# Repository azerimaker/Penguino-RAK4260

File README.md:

# Penguino-RAK4260
This repo contains all the necessary design and fabrication files for the Penguino 4260 SAMR34 Feather breakout board. 

First prototypes are being sold on [Tindie](https://www.tindie.com/products/21143/) and some more info can also be found on the corresponding [hackaday.io](https://hackaday.io/project/168876-penguino-feather-samr34-lora-dev-board) project page. This Penguino version uses [RAK4260](https://rakwireless.kckb.st/9e150da0) module. 

________________________________

### Current HW version is:
Penguino Feather v1.2. 
- Comes with green soldermask
- Adds CH340E USB-UART Converter IC

________________________________

### Example Firmware

Povided example in the *Firmware* directory contains ready to use example projetcs for Atmel Studio v7.
- RGB LED Toggle 
- LoRaWAN UART Demo

## License:
- Hardware license: CERN-OHL-S v2
- Software license: under MIT unless otherise indicated 
- Documentation license:  CC BY-SA 4.0 International.
________________________________
## Open Source Hardware
This board is an OSHWA approved design: [AZ000001](https://certification.oshwa.org/az000001.html)

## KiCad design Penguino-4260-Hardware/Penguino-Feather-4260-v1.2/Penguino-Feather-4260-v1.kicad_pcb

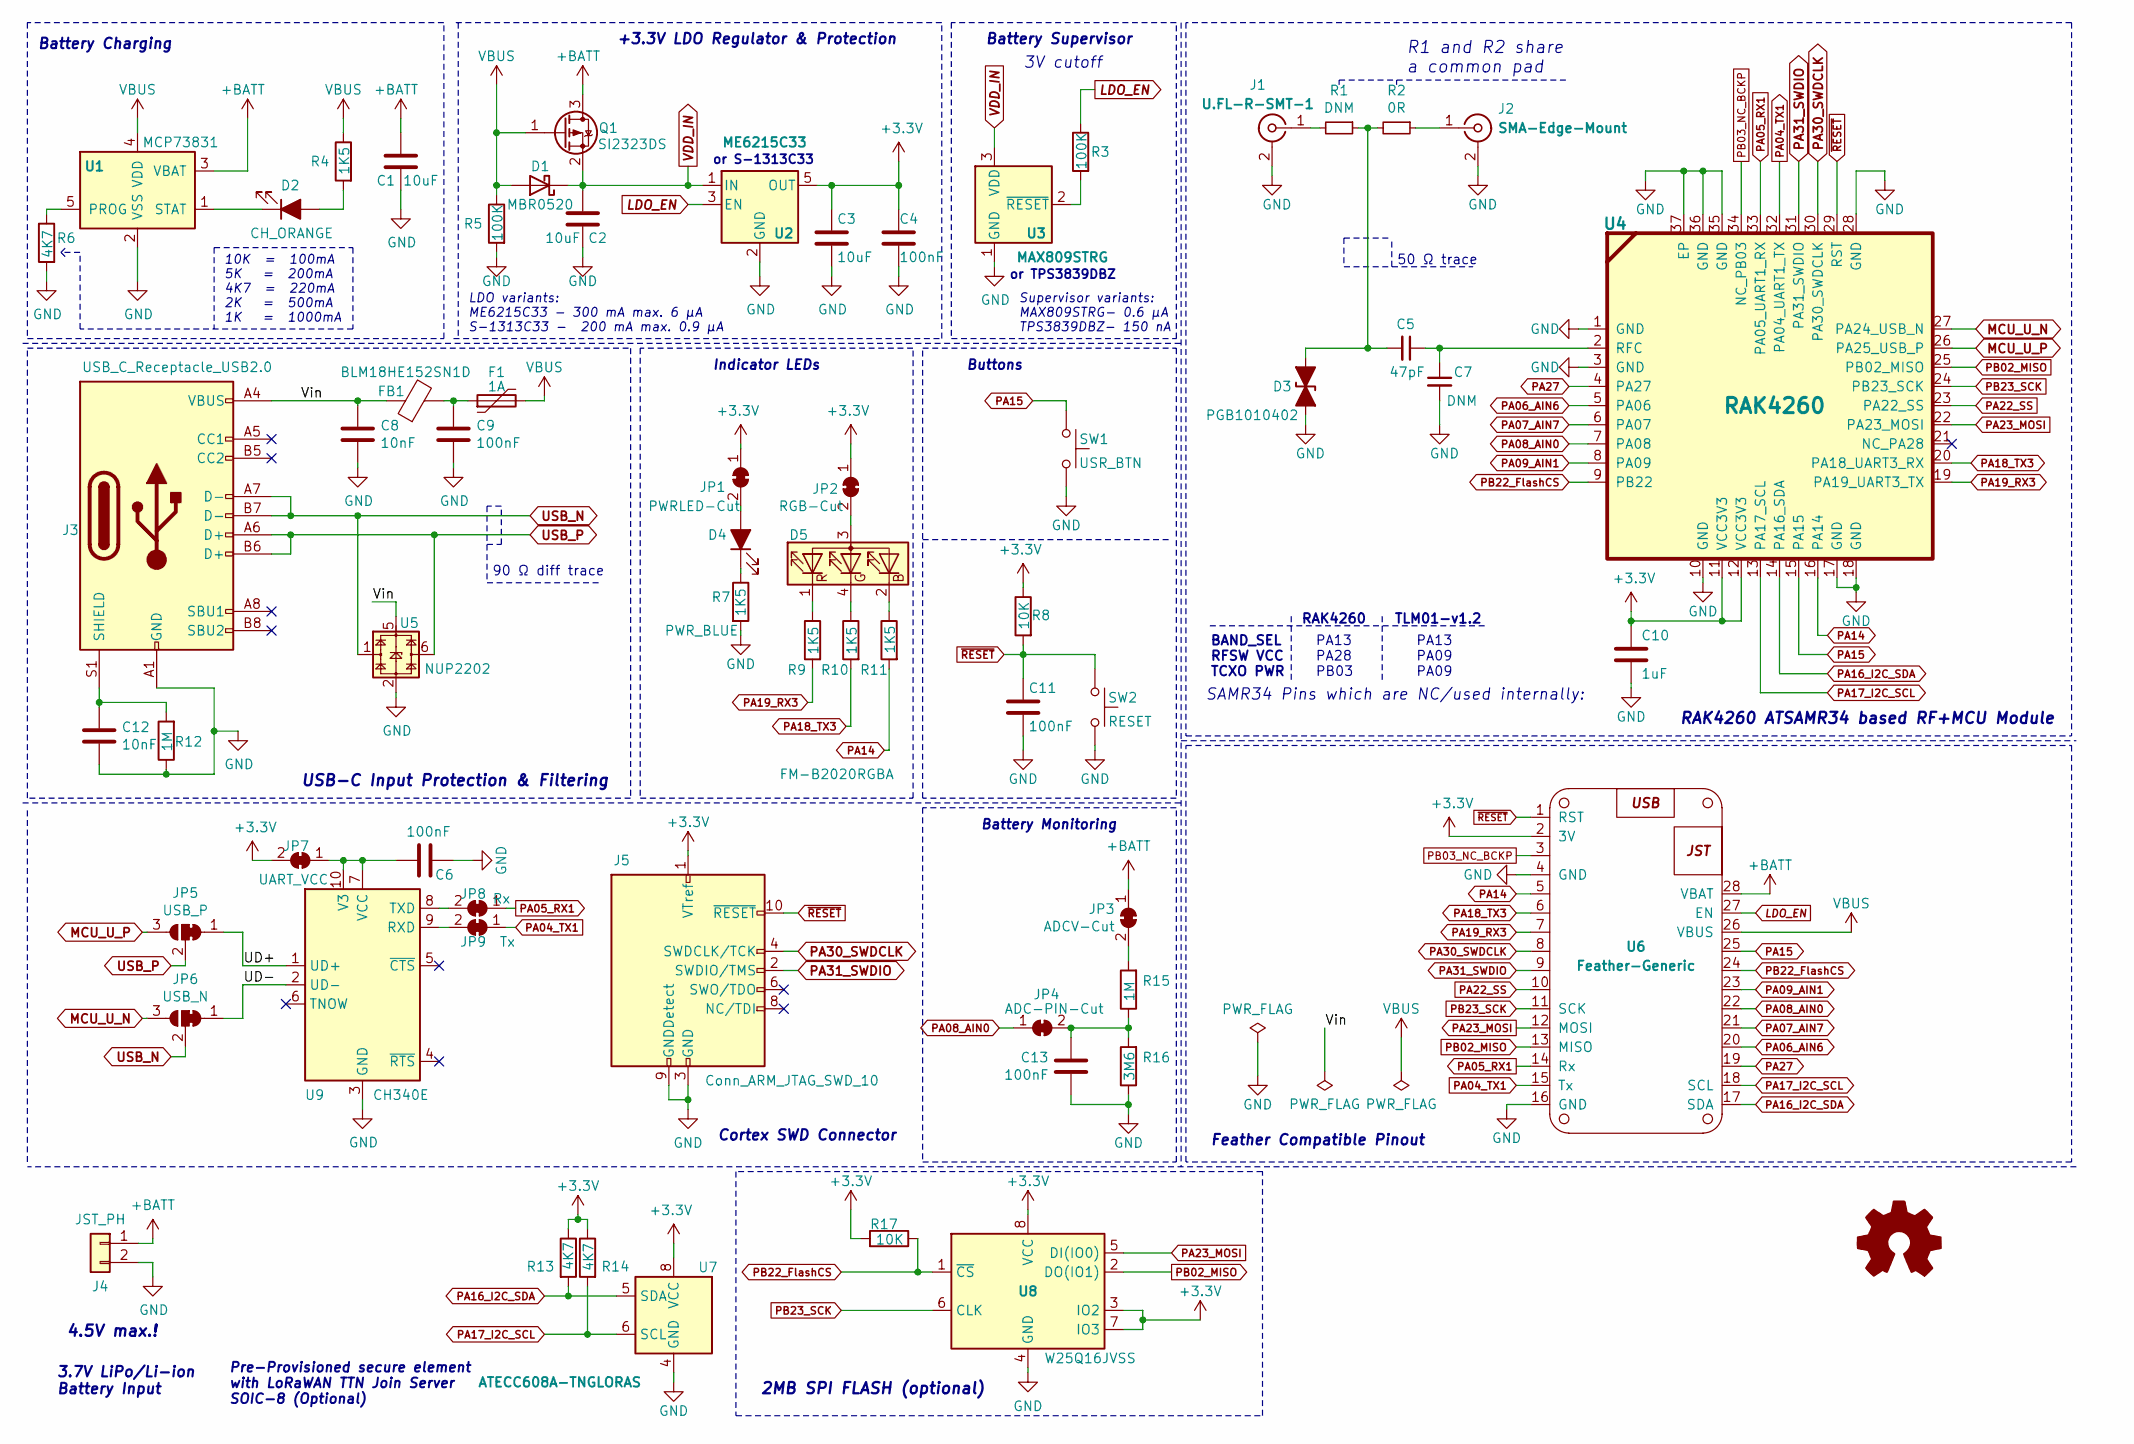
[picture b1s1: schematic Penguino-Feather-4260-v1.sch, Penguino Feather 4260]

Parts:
C1, C2, C3: 10uF; C_0603_1608Metric
C4, C6, C9: 100nF; C_0603_1608Metric; MPN CC0603KRX7R9BB104
C5: 47pF; C_0402_1005Metric
C7: DNM; C_0402_1005Metric
C8, C12: 10nF; C_0603_1608Metric; MPN CC0603KRX7R9BB103
C10: 1uF; C_0603_1608Metric; MPN CC0603KRX7R8BB105
C11, C13: 100nF; C_0402_1005Metric; MPN CC0603KRX7R9BB104
D1: MBR0520; D_SOD-123; MPN MBR0520
D2: CH_ORANGE; LED_0603_1608Metric
D3: PGB1010402; L_0402_1005Metric; MPN PGB1010402KR
D4: PWR_BLUE; LED_0603_1608Metric
D5: FM-B2020RGBA; LED_Cree-PLCC4_2x2mm_CW; MPN FM-B2020RGBA-HG
F1: 1A; Fuse_0805_2012Metric; MPN 0805L110SLYR
FB1: BLM18HE152SN1D; L_0603_1608Metric; MPN BLM18HE152SN1D
J1: U.FL-R-SMT-1; U.FL_Hirose_U.FL-R-SMT-1_Vertical; MPN U.FL-R-SMT-1(80)
J2: SMA-Edge-Mount; SMA_J_P_X_ST_EM1_EdgeMount; MPN SMA-J-P-H-ST-EM1
J3: USB_C_Receptacle_USB2.0; USB_C_Receptacle_Palconn_UTC16-G; MPN TYPE-C-31-M-12
J4: JST_PH; JST_PH_S2B-PH-SM4-TB_1x02-1MP_P2.00mm_Horizontal; MPN S2B-PH-SM4-TB(LF)(SN)
J5: Conn_ARM_JTAG_SWD_10; PinHeader_2x05_P1.27mm_Vertical_SMD
JP1: PWRLED-Cut; SolderJumper-2_P1.3mm_Bridged_RoundedPad1.0x1.5mm
JP2: RGB-Cut; SolderJumper-2_P1.3mm_Bridged_RoundedPad1.0x1.5mm
JP3: ADCV-Cut; SolderJumper-2_P1.3mm_Bridged_RoundedPad1.0x1.5mm
JP4: ADC-PIN-Cut; SolderJumper-2_P1.3mm_Bridged_RoundedPad1.0x1.5mm
JP5: USB_P; SolderJumper-3_P1.3mm_Bridged12_Pad1.0x1.5mm
JP6: USB_N; SolderJumper-3_P1.3mm_Bridged12_Pad1.0x1.5mm
JP7: UART_VCC; SolderJumper-2_P1.3mm_Bridged_RoundedPad1.0x1.5mm
JP8: Rx; SolderJumper-2_P1.3mm_Bridged_RoundedPad1.0x1.5mm
JP9: Tx; SolderJumper-2_P1.3mm_Bridged_RoundedPad1.0x1.5mm
Q1: SI2323DS; SOT-23; MPN SI2323DS-T1-E3
R1: DNM; R_0402_1005Metric
R2: 0R; R_0402_1005Metric
R3, R5: 100K; R_0402_1005Metric
R4, R7, R9, R10, R11: 1K5; R_0402_1005Metric
R6, R13, R14: 4K7; R_0402_1005Metric
R8, R17: 10K; R_0402_1005Metric
R12, R15: 1M; R_0402_1005Metric
R16: 3M6; R_0402_1005Metric; MPN RC0402JR-073M6L
SW1: USR_BTN; SW_Push_SKRPACE010; MPN SKRPACE010
SW2: RESET; SW_Push_SKRPACE010; MPN SKRPACE010
U1: MCP73831; SOT-23-5; MPN MCP73831-2-OT
U2: ME6215C33; SOT-23-5; MPN ME6215C33
U3: MAX809STRG; SOT-23; MPN MAX809STRG
U4: RAK4260; RAK4260-footprint_w_solder_paste
U5: NUP2202; SOT-363_SC-70-6; MPN NUP2202W1T2G
U6: Feather-Generic
U7: ATECC608A-TNGLORAS; SOIC-8_3.9x4.9mm_P1.27mm; MPN ATECC608A-TNGLORAS-B
U8: W25Q16JVSS; SOIC-8_5.23x5.23mm_P1.27mm
U9: CH340E; MSOP-10_3x3mm_P0.5mm

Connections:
+3V3: C3.1, C4.1, C10.1, J5.1 (VTref), JP1.1 (A), JP2.1 (A), JP7.2 (B), R8.1, R13.1, R14.1, R17.2, U2.5 (OUT), U4.11 (VCC3V3), U4.12 (VCC3V3), U6.2 (3V), U7.8 (VCC), U8.3 (IO2), U8.7 (IO3), U8.8 (VCC)
+BATT: C1.1, J4.1, JP3.1 (A), Q1.3 (D), U1.3 (VBAT), U6.28 (VBAT)
/UD+: JP5.1 (A), U9.1 (UD+)
/UD-: JP6.1 (A), U9.2 (UD-)
/Vin: C8.1, FB1.1, J3.A4 (VBUS), J3.A9 (VBUS), J3.B4 (VBUS), J3.B9 (VBUS), U5.5
GND: C1.2, C2.2, C3.2, C4.2, C6.1, C7.2, C8.2, C9.2, C10.2, C11.2, C12.1, C13.1, D3.2 (A2), J1.2 (Ext), J2.2 (Ext), J3.A1 (GND), J3.A12 (GND), J3.B1 (GND), J3.B12 (GND), J4.2, J5.3 (GND), J5.5 (GND), J5.9 (GNDDetect), R5.2, R6.2, R7.2, R12.1, R16.1, SW1.1, SW2.1, U1.2 (VSS), U2.2 (GND), U3.1 (GND), U4.1 (GND), U4.3 (GND), U4.10 (GND), U4.17 (GND), U4.18 (GND), U4.28 (GND), U4.35 (GND), U4.36 (GND), U4.37 (EP), U5.2, U6.4 (GND), U6.16 (GND), U7.4 (GND), U8.4 (GND), U9.3 (GND)
LDO_EN: R3.1, U2.3 (EN), U6.27 (EN)
MCU_U_N: JP6.3 (B), U4.27 (PA24_USB_N)
MCU_U_P: JP5.3 (B), U4.26 (PA25_USB_P)
unnamed: C5.1, C7.1, U4.2 (RFC)
unnamed: C5.2, D3.1 (A1), R1.1, R2.2
unnamed: C6.2, JP7.1 (A), U9.7 (VCC), U9.10 (V3)
unnamed: C9.1, F1.1, FB1.2
unnamed: C12.2, J3.S1 (SHIELD), R12.2
unnamed: C13.2, JP4.2 (B), R15.1, R16.2
unnamed: D2.1 (K), U1.1 (STAT)
unnamed: D2.2 (A), R4.2
unnamed: D4.1 (K), R7.1
unnamed: D4.2 (A), JP1.2 (B)
unnamed: D5.1 (RK), R9.1
unnamed: D5.2 (BK), R11.1
unnamed: D5.3 (A), JP2.2 (B)
unnamed: D5.4 (GK), R10.1
unnamed: J1.1 (In), R1.2
unnamed: J2.1 (In), R2.1
unnamed: JP3.2 (B), R15.2
unnamed: JP8.2 (B), U9.8 (TXD)
unnamed: JP9.2 (B), U9.9 (RXD)
unnamed: R3.2, U3.2 (~RESET)
unnamed: R6.1, U1.5 (PROG)
PA04_TX1: JP9.1 (A), U4.32 (PA04_UART1_TX), U6.15 (Tx)
PA05_RX1: JP8.1 (A), U4.33 (PA05_UART1_RX), U6.14 (Rx)
PA06_AIN6: U4.5 (PA06), U6.20
PA07_AIN7: U4.6 (PA07), U6.21
PA08_AIN0: JP4.1 (A), U4.7 (PA08), U6.22
PA09_AIN1: U4.8 (PA09), U6.23
PA14: R11.2, U4.16 (PA14), U6.5
PA15: SW1.2, U4.15 (PA15), U6.25
PA16_I2C_SDA: R13.2, U4.14 (PA16_SDA), U6.17 (SDA), U7.5 (SDA)
PA17_I2C_SCL: R14.2, U4.13 (PA17_SCL), U6.18 (SCL), U7.6 (SCL)
PA18_TX3: R10.2, U4.20 (PA18_UART3_RX), U6.6
PA19_RX3: R9.2, U4.19 (PA19_UART3_TX), U6.7
PA22_SS: U4.23 (PA22_SS), U6.10
PA23_MOSI: U4.22 (PA23_MOSI), U6.12 (MOSI), U8.5 (DI(IO0))
PA27: U4.4 (PA27), U6.19
PA30_SWDCLK: J5.4 (SWDCLK/TCK), U4.30 (PA30_SWDCLK), U6.8
PA31_SWDIO: J5.2 (SWDIO/TMS), U4.31 (PA31_SWDIO), U6.9
PB02_MISO: U4.25 (PB02_MISO), U6.13 (MISO), U8.2 (DO(IO1))
PB03_NC_BCKP: U4.34 (NC_PB03), U6.3
PB22_FlashCS: R17.1, U4.9 (PB22), U6.24, U8.1 (~CS)
PB23_SCK: U4.24 (PB23_SCK), U6.11 (SCK), U8.6 (CLK)
USB_N: J3.A7 (D-), J3.B7 (D-), JP6.2 (C), U5.1
USB_P: J3.A6 (D+), J3.B6 (D+), JP5.2 (C), U5.6
VBUS: D1.2 (A), F1.2, Q1.1 (G), R4.1, R5.1, U1.4 (VDD), U6.26 (VBUS)
VDD_IN: C2.1, D1.1 (K), Q1.2 (S), U2.1 (IN), U3.3 (VDD)
~RESET: C11.1, J5.10 (~RESET~), R8.2, SW2.2, U4.29 (RST), U6.1 (RST)

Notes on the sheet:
10K = 100mA 5K = 200mA 4K7 = 220mA 2K = 500mA 1K = 1000mA
3.7V LiPo/Li-ion Battery Input
Battery Charging
USB-C Input Protection & Filtering
Indicator LEDs
RAK4260 ATSAMR34 based RF+MCU Module
Feather Compatible Pinout
Battery Monitoring
R1 and R2 share a common pad
Cortex SWD Connector
90 Ω diff trace
50 Ω trace
SAMR34 Pins which are NC/used internally:
Pre-Provisioned secure element with LoRaWAN TTN Join Server SOIC-8 (Optional)
Buttons
+3.3V LDO Regulator & Protection
Battery Supervisor
LDO variants: ME6215C33 - 300 mA max. 6 μA S-1313C33 - 200 mA max. 0.9 μA
3V cutoff
or TPS3839DBZ
or S-1313C33
Supervisor variants: MAX809STRG- 0.6 μA TPS3839DBZ- 150 nA
2MB SPI FLASH (optional)
BAND_SEL RFSW VCC TCXO PWR
PA13 PA28 PB03
PA13 PA09 PA09
RAK4260 TLM01-v1.2
4.5V max.!

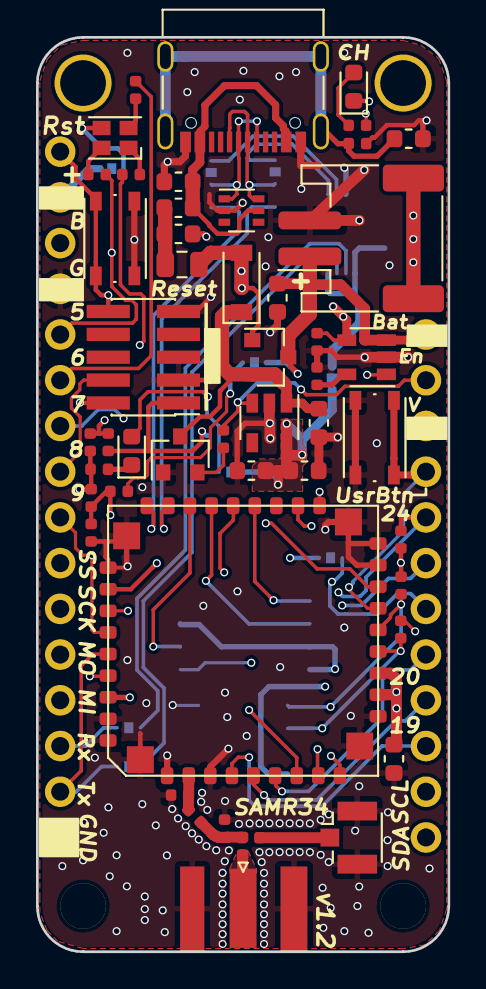
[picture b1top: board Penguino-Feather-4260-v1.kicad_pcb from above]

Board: 4 copper layers, 22.9 x 50.8 mm, 63 parts (0 on the bottom side), 56 nets.

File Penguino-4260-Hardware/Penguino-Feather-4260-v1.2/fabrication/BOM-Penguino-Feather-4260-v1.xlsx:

Name: | Penguino-Feather-4260-v1.2
Date:
Tool: | Eeschema (5.1.6)
Total Component Count: | 51
Unique Component Count: | 35
Item | Qty | Reference(s) | MPN | Alternative Part | Value | Footprint | URL | URL (alt)
1 | 3 | C1, C2, C3 | CL10A106MO8NQNC |  | 10uF | Capacitor_SMD:C_0603_1608Metric | https://lcsc.com/product-detail/Multilayer-Ceramic-Capacitor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 | ~
2 | 3 | C4, C6, C9 | CC0603KRX7R9BB104 |  | 100nF | Capacitor_SMD:C_0603_1608Metric | https://lcsc.com/product-detail/Multilayer-Ceramic-Capacitor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 | ~
3 | 1 | C5 | GJM1555C1H470JB01D |  | 47pF | Capacitor_SMD:C_0402_1005Metric | https://lcsc.com/product-detail/Multilayer-Ceramic-Capacitor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 | ~
4 |  | C7 | - |  | DNM | Capacitor_SMD:C_0402_1005Metric |  | ~
5 | 2 | C8, C12 | CC0603KRX7R9BB103 |  | 10nF | Capacitor_SMD:C_0603_1608Metric | https://lcsc.com/product-detail/Multilayer-Ceramic-Capacitor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 | ~
6 | 1 | C10 | CC0603KRX7R8BB105 |  | 1uF | Capacitor_SMD:C_0603_1608Metric | https://lcsc.com/product-detail/Others_YAGEO-CC0603KRX7R8BB1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 | ~
7 | 2 | C11, C13 | CC0402MRY5V8BB104 |  | 100nF | Capacitor_SMD:C_0402_1005Metric | https://lcsc.com/product-detail/Others_YAGEO-CC0402MRY5V8BB1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 | ~
8 | 1 | D1 | MBR0520 |  | MBR0520 | Diode_SMD:D_SOD-123 | https://lcsc.com/product-detail/Schottky-Barrier-Diodes-SBD_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 | ~
9 | 1 | D2 | 19-217/S2C-AL1M2VY/3T |  | CH_ORANGE | LED_SMD:LED_0603_1608Metric | https://lcsc.com/product-detail/Others_Everlight-Elec-19-217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 | ~
10 | 1 | D3 | PGB1010402KR |  | PGB1010402 | Inductor_SMD:L_0402_1005Metric | https://lcsc.com/product-detail/Diodes-ESD_Littelfuse-PGB101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 | ~
11 | 1 | D4 | FC-DA1608BK-470H10 |  | PWR_BLUE | LED_SMD:LED_0603_1608Metric | https://lcsc.com/product-detail/Light-Emitting-Diodes-LED_Bl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 | ~
12 | 1 | D5 | FM-B2020RGBA-HG |  | RGB LED 2020 | LED_SMD:LED_Cree-PLCC4_2x2mm_CW | https://lcsc.com/product-detail/Light-Emitting-Diodes-LED_Fo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 | ~
13 | 1 | F1 | 0805L110SLYR |  | 1A | Fuse:Fuse_0805_2012Metric | https://lcsc.com/product-detail/Surface-Mount-Fuses_Littelfu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 | ~
14 | 1 | FB1 | BLM18HE152SN1D |  | BLM18HE152SN1D | Inductor_SMD:L_0603_1608Metric | https://lcsc.com/product-detail/Ferrite-Beads-And-Chips_muRa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 | ~
15 | 1 | J1 | U.FL-R-SMT-1(80) |  | U.FL-R-SMT-1 | Connector_Coaxial:U.FL_Hirose_U.FL-R-SMT-1_Vertical | https://lcsc.com/product-detail/_Hirose_U-FL-R-SMT-1-80_Hiro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 | ~
16 | 1 | J2 | SMA-J-P-H-ST-EM1 |  | SMA-Edge-Mount | tinylora_v1:SMA_J_P_X_ST_EM1_EdgeMount | https://www.ebay.com/itm/293146230861 | ~
17 | 1 | J3 | TYPE-C-31-M-12 |  | USB_C_Receptacle_USB2.0 | Connector_USB:USB_C_Receptacle_Palconn_UTC16-G | https://lcsc.com/product-detail/USB-Connectors_Korean-Hropar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 | ~
18 | 1 | J4 | S2B-PH-SM4-TB(LF)(SN) |  | JST_PH | Connector_JST:JST_PH_S2B-PH-SM4-TB_1x02-1MP_P2.00mm_Horizontal | https://www.aliexpress.com/item/32513477927.html?spm=a2g0o.c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 | ~
19 | 1 | J5 | - | FTSH-105-01-F-DV-K | Male PCB Header Dual row | Connector_PinHeader_1.27mm:PinHeader_2x05_P1.27mm_Vertical_SMD | https://www.aliexpress.com/item/-/33030461496.html?spm=a2g0o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 | https://www.digikey.com/product-detail/en/samtec-inc/FTSH-10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
20 | 1 | Q1 | SI2323DS-T1-E3 |  | SI2323DS | Package_TO_SOT_SMD:SOT-23 | https://lcsc.com/product-detail/MOSFET_Vishay-Intertech-SI23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 | ~
21 |  | R1 | - | 0R | DNM | Resistor_SMD:R_0402_1005Metric | https://lcsc.com/product-detail/Chip-Resistor-Surface-Mount_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 | ~
22 | 1 | R2 | RC0402JR-070RL |  | 0R | Resistor_SMD:R_0402_1005Metric | https://lcsc.com/product-detail/Chip-Resistor-Surface-Mount_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 | ~
23 | 2 | R3, R5 | RC0402JR-07100KL |  | 100K | Resistor_SMD:R_0402_1005Metric | https://lcsc.com/product-detail/Chip-Resistor-Surface-Mount_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 | ~
24 | 5 | R4, R7, R9, R10, R11 | RC0402FR-071K5L |  | 1K5 | Resistor_SMD:R_0402_1005Metric | https://lcsc.com/product-detail/Chip-Resistor-Surface-Mount_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 | ~
25 | 3 | R6, R13, R14 | RC0402FR-074K7L |  | 4K7 | Resistor_SMD:R_0402_1005Metric | https://lcsc.com/product-detail/Chip-Resistor-Surface-Mount_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 | ~
26 | 2 | R8, R17 | RC0402FR-0710KL |  | 10K | Resistor_SMD:R_0402_1005Metric | https://lcsc.com/product-detail/Chip-Resistor-Surface-Mount_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 | ~
27 | 2 | R12, R15 | 0402WGF1004TCE |  | 1M | Resistor_SMD:R_0402_1005Metric | https://lcsc.com/product-detail/Chip-Resistor-Surface-Mount_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 | ~
28 | 1 | R16 | RC0402JR-073M6L |  | 3M6 | Resistor_SMD:R_0402_1005Metric | https://lcsc.com/product-detail/Chip-Resistor-Surface-Mount_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 | ~
29 | 2 | SW1, SW2 | SKRPACE010 |  | USR_BTN, RESET | switch-footprints:SW_Push_SKRPACE010 | https://lcsc.com/product-detail/Tactile-Switches_ALPS_SKRPAC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 | ~
30 | 1 | U1 | MCP73831-2ACI-OT |  | LiPo battery charger IC | Package_TO_SOT_SMD:SOT-23-5 | https://lcsc.com/product-detail/PMIC-Battery-Management_Micr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 | ~
31 | 1 | U2 | S-1313D33 | ME6215C33 | +3.3V LDO Regulator | Package_TO_SOT_SMD:SOT-23-5 | https://lcsc.com/product-detail/Low-Dropout-Regulators-LDO_M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 | https://www.mouser.de/ProductDetail/ABLIC/S-1313C33-M5T1U3?q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
32 | 1 | U3 | TPS3839K33DBZR | MAX809STRG | 3V Voltage Supervisor | Package_TO_SOT_SMD:SOT-23 | https://lcsc.com/product-detail/Microprocessor-Microcontroll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 | https://lcsc.com/product-detail/PMIC-Supervisors_TI_TPS3839K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
33 | 1 | U4 | RAK4260 |  | RAK4260 | rak4260:RAK4260-footprint_w_solder_paste | https://store.rakwireless.com/products/rak4260-lora-module | ~
34 | 1 | U5 | NUP2202W1T2G |  | NUP2202 | Package_TO_SOT_SMD:SOT-363_SC-70-6 | https://lcsc.com/product-detail/TVS_ON-Semicon_NUP2202W1T2G_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 | ~
35 | 1 | U7 | ATECC608A-TNGLORAS-B |  | TTN Secure Element | Package_SO:SOIC-8_3.9x4.9mm_P1.27mm | https://www.microchipdirect.com/product/ATECC608A-TNGLORA | ~
36 | 1 | U8 | W25Q16JVSS |  | 2MB Flash Memory | Package_SO:SOIC-8_5.23x5.23mm_P1.27mm | https://lcsc.com/product-detail/FLASH_Winbond-Elec-W25Q16JVS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 | ~
37 | 1 | U9 | CH340E |  | USB UART Converter | Package_SO:MSOP-10_3x3mm_P0.5mm

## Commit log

2020-04-12 Penguino 4360 files added
    Dedicated Repo for the 4260 version
2020-04-24 CERN-OHL-S v2 added
2020-04-24 readme fix
2020-08-19 Readme updates
2020-08-19 Fix: README
2020-10-29 doc: Folder structure update
2020-10-29 sch, pcb: v1.2 updates
2020-10-29 lib: directory updates
2020-10-29 fw: Project cleanup
2020-10-30 doc: Readme update
2020-12-14 Changed Pin number assignments to RGB LEDs
2020-12-16 fix: RGB LED pin mapping update
2020-12-16 fix: AS7 solution renaming
